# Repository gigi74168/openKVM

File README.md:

# openKVM

**Un mini KVM-over-IP ouvert, matériel compris, sans écran.** Tu le branches sur le HDMI et l'USB d'une machine, et tu la
pilotes depuis un navigateur : image, clavier, souris, démarrage sur une image ISO, jusque dans le BIOS.
Sur le boîtier : deux LED et un bouton, rien d'autre.

| Carte (pré-placement) | Boîtier (concept) |
|---|---|
|  |  |

> ⚠️ **État du projet : en conception.** Rien n'a encore été fabriqué ni testé. Les images ci-dessus sont des
> **rendus** : la carte est pré-placée mais **pas routée**, et le boîtier est un concept. Ne lance aucune fabrication
> à partir de ces fichiers sans la revue humaine décrite dans [`docs/04`](docs/04-schema-electronique.md#6-points-à-faire-relire-par-un-humain-avant-fabrication).

## En bref

| | openKVM v1 (visé) | JetKVM Mini (référence) |
|---|---|---|
| SoC | ESP32-P4NRW32X, 32 Mo de PSRAM | ESP32-P4X, 32 Mo de PSRAM |
| Vidéo | HDMI 1080p30 / 720p60, H.264 matériel | idem |
| Capture | TC358743, CSI-2 2 voies | idem |
| Réseau | Ethernet 10/100 (IP101GRI) | idem |
| USB cible | USB 2.0 High Speed : clavier, souris, stockage, audio | idem |
| microSD | Slot UHS-I (ISO plus rapides, à mesurer) | Slot standard |
| Écran | **Aucun** : LED d'alimentation + LED d'état, appareil trouvé par son nom réseau (mDNS, à venir avec le firmware) | IPS 240 × 240 |
| Boutons | 1 latéral (réinitialisation) + BOOT interne | 2 latéraux |
| Taille | PCB 45 × 45 mm ; boîtier ≈ 49,6 × 49,6 × 21,5 mm imprimé en 3D | 42 × 42 × 23 mm, aluminium |
| Matériel | **Ouvert : CERN-OHL-S-2.0** | Non publié |
| Firmware | Fork MIT du firmware du Mini, pilote d'écran retiré (à venir) | MIT |
| Prix | Objectif < 39 $ : **hors d'atteinte à 5–8 cartes**, jouable vers 20 cartes (voir [`docs/05`](docs/05-bom-chiffree.md)) | 39 $ ; 33 $ par 3 |

Pas de Gigabit en v1 : ni l'ESP32-P4 ni le RV1106 du JetKVM original ne le permettent.
L'explication est dans [`docs/00`](docs/00-decision-architecture.md).

## Architecture

## La carte

| Dessus | Vue arrière |
|---|---|
|  |  |

- **Arrière** : RJ45, HDMI, USB-C vers la machine cible.
- **Gauche** : USB-C « EXT » (alimentation, flashage, debug).
- **Droite** : microSD et bouton FN.
- **Avant** : LED d'alimentation (verte) et LED d'état (jaune).
- **Dessus** : capot plein, ouïes d'aération.

Le fichier [`hardware/openkvm.kicad_pcb`](hardware/openkvm.kicad_pcb) contient le contour, les 180 composants et tous
les nets. Les connecteurs et les puces principales sont placés ; **le routage reste à faire**.

## Le schéma

Six pages, disponibles en [PDF](hardware/exports/openkvm-schema.pdf) et dans KiCad 9.

| | |
|---|---|
|  Alimentation |  ESP32-P4 |
|  Capture HDMI |  Ethernet |
|  Périphériques |  Vue d'ensemble |

Le schéma est généré depuis une description texte ([`design.py`](hardware/scripts/design.py)), puis KiCad en
ré-extrait la netlist pour la comparer à la source : **706 broches, 0 différence**.

## Le boîtier

| Arrière | Avant et côté droit |
|---|---|
|  |  |

[`mechanical/openkvm-boitier-concept.scad`](mechanical/openkvm-boitier-concept.scad) est un modèle **paramétrique OpenSCAD**
qui sert d'aperçu : coque, capot plein à ouïes, découpes des connecteurs, deux trous de LED en façade. Les cotes définitives viendront au livrable 7,
une fois la carte routée. Pour ta propre CAO, la carte avec tous ses composants est dans
[`mechanical/openkvm-pcb-preplacement.step.zip`](mechanical/openkvm-pcb-preplacement.step.zip) (STEP, 3,3 Mo compressé)
et en [`GLB`](mechanical/openkvm-pcb-preplacement.glb) pour Blender ou un visualiseur web.

### Modèles 3D des composants

Chaque composant a un modèle dans [`hardware/lib/openkvm.3dshapes/`](hardware/lib/openkvm.3dshapes/) : 16 en **STEP et VRML**
(pièces LCSC, issues d'EasyEDA) et le BGA du TC358743, dessiné ici ([`gen_3d_bga.py`](hardware/scripts/gen_3d_bga.py)).
Deux sont **approximatifs**, à remplacer par ceux du fabricant pour tes cotes définitives :

- **TC358743 (BGA-64)** : corps 6 × 6 mm, épaisseur générique de 0,75 mm, **hauteur non vérifiée** sur la fiche technique ;
- **Oscillateur 27 MHz (Y2)** : forme générique 3,2 × 2,5 mm empruntée à l'oscillateur 40 MHz.

Le BGA n'existe qu'en VRML (KiCad ne sait pas l'exporter seul en STEP) ; il est inclus dans le STEP de la carte.

## Contenu du dépôt

```
docs/                       Les livrables, un par étape, avec leurs sources
  00-decision-architecture.md   Pourquoi ESP32-P4 et pas de Gigabit
  01-recherche-kvm-existants.md Comparatif JetKVM, NanoKVM, PicoKVM, PiKVM, Comet
  02-choix-soc-capture.md       ESP32-P4X et TC358743 : prix, stock, risques
  03-cahier-des-charges.md      Exigences, interfaces, budget de courant
  04-schema-electronique.md     Schéma, notes par bloc, points à relire
  05-bom-chiffree.md            BOM chiffrée, coût par carte, contraintes JLCPCB
  images/                       Rendus et diagrammes (sources dans images/src/)
hardware/                   Projet KiCad 9
  openkvm.kicad_pro/.kicad_sch  Schéma (5 feuilles)
  openkvm.kicad_pcb             Carte pré-placée, non routée
  fabrication/                  BOM JLCPCB, BOM chiffrée, instantané des prix
  exports/                      PDF du schéma, netlist et liste de composants en CSV
  lib/                          Symboles, empreintes, modèles 3D (.wrl + .step)
  scripts/                      design.py (source), générateurs, vérification
  build.sh                      Régénère tout
mechanical/                 Concept de boîtier (OpenSCAD), carte en STEP et en GLB
LICENSES/, LICENSE.md, NOTICE.md
```

## Utiliser les fichiers

**Ouvrir le projet** : KiCad 9, puis `hardware/openkvm.kicad_pro`.

**Régénérer** après une modification de `design.py` (il faut KiCad 9 avec `kicad-cli` et le module Python `pcbnew`) :

```bash
cd hardware && ./build.sh
```

Attention : `build.sh` réécrit `openkvm.kicad_pcb`. Une fois ton routage commencé, ne relance que le schéma
(`python3 scripts/gen_kicad.py`) et utilise « Mettre à jour le PCB depuis le schéma » dans KiCad.

**Commander chez JLCPCB**, quand la carte sera routée et relue :

| Fichier demandé par JLCPCB | Où | État |
|---|---|---|
| BOM | [`hardware/fabrication/openkvm-bom-jlcpcb.csv`](hardware/fabrication/openkvm-bom-jlcpcb.csv) | Prête, 1 ligne sans code LCSC (TC358743, à fournir) |
| Gerbers et perçages | À exporter depuis KiCad après routage | À faire |
| Fichier de placement (CPL) | À exporter depuis KiCad après routage | À faire |

## Avancement

| # | Livrable | État |
|---|---|---|
| 0 | Décision d'architecture | ✅ [`docs/00`](docs/00-decision-architecture.md) |
| 1 | Recherche sur les KVM existants | ✅ [`docs/01`](docs/01-recherche-kvm-existants.md) |
| 2 | Choix du SoC et de la puce de capture | ✅ [`docs/02`](docs/02-choix-soc-capture.md) |
| 3 | Cahier des charges et diagramme de blocs | ✅ [`docs/03`](docs/03-cahier-des-charges.md) |
| 4 | Schéma électronique | 🟡 rév. 0.2 (sans écran), à relire : [`docs/04`](docs/04-schema-electronique.md) |
| 5 | BOM chiffrée (prix sur 5 pièces) | 🟡 rév. 0.2 (sans écran), à valider : [`docs/05`](docs/05-bom-chiffree.md) |
| 6 | Spécifications de layout | ⏳ |
| 7 | Cotes du boîtier | ⏳ concept disponible |
| 8 | Firmware (fork du JetKVM Mini) | ⏳ |
| 9 | Plan de test et de mise en route | ⏳ |

## Risques connus

- **TC358743 obsolète** : introuvable chez LCSC, à acheter chez un broker (risque de contrefaçon).
- **HDMI, USB High Speed, MIPI** : signaux rapides, le routage demandera des impédances contrôlées.
- **BGA au pas de 0,65 mm** et QFN-104 : assemblage délicat, radiographie conseillée.
- **Consommation** : 0,52 à 0,57 A estimés sous 5 V, au-dessus des 500 mA d'un port USB 2.0.
- **Pas d'écran** : sans mDNS ou accès au routeur, l'adresse IP de l'appareil ne se devine pas. À traiter dans le firmware.
- **Aucune certification CE/FCC** : prototypes à usage personnel.
- **HDCP non géré** : les contenus protégés donneront un écran noir.

## Licences

Matériel sous **CERN-OHL-S-2.0**, scripts sous **MIT**, documentation sous **CC-BY-SA-4.0**.
Détail dans [`LICENSE.md`](LICENSE.md), éléments repris de tiers dans [`NOTICE.md`](NOTICE.md).

« JetKVM » est une marque de BuildJet, Inc. openKVM est un projet indépendant.

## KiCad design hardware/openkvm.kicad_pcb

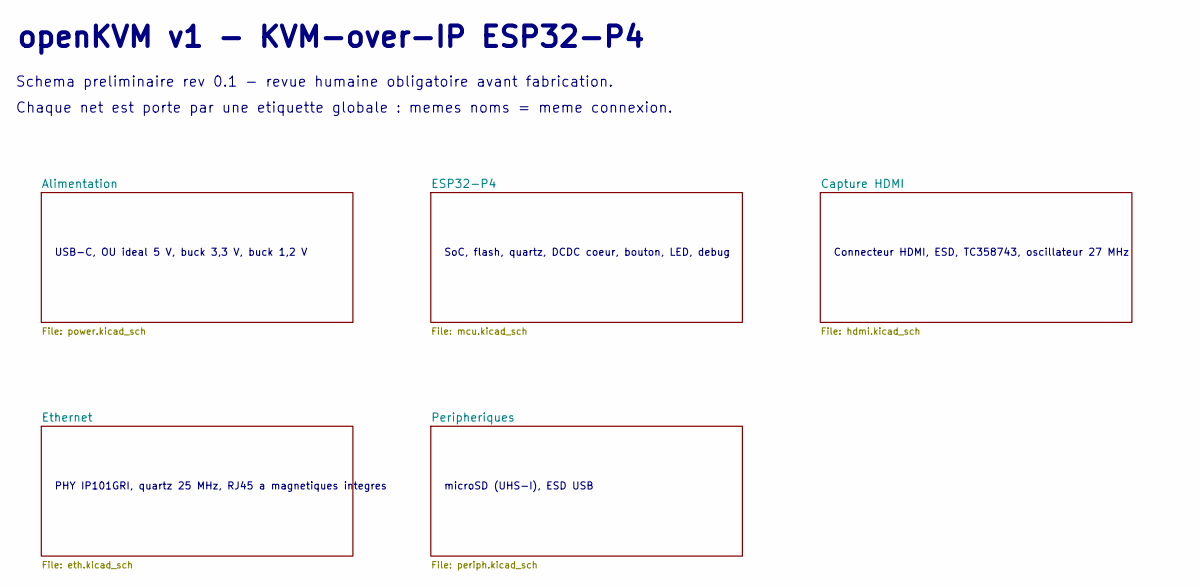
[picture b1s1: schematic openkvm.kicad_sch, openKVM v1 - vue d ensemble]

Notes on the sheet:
openKVM v1 - KVM-over-IP ESP32-P4
Schema preliminaire rev 0.1 - revue humaine obligatoire avant fabrication.
Chaque net est porte par une etiquette globale : memes noms = meme connexion.
USB-C, OU ideal 5 V, buck 3,3 V, buck 1,2 V
SoC, flash, quartz, DCDC coeur, bouton, LED, debug
Connecteur HDMI, ESD, TC358743, oscillateur 27 MHz
PHY IP101GRI, quartz 25 MHz, RJ45 a magnetiques integres
microSD (UHS-I), ESD USB

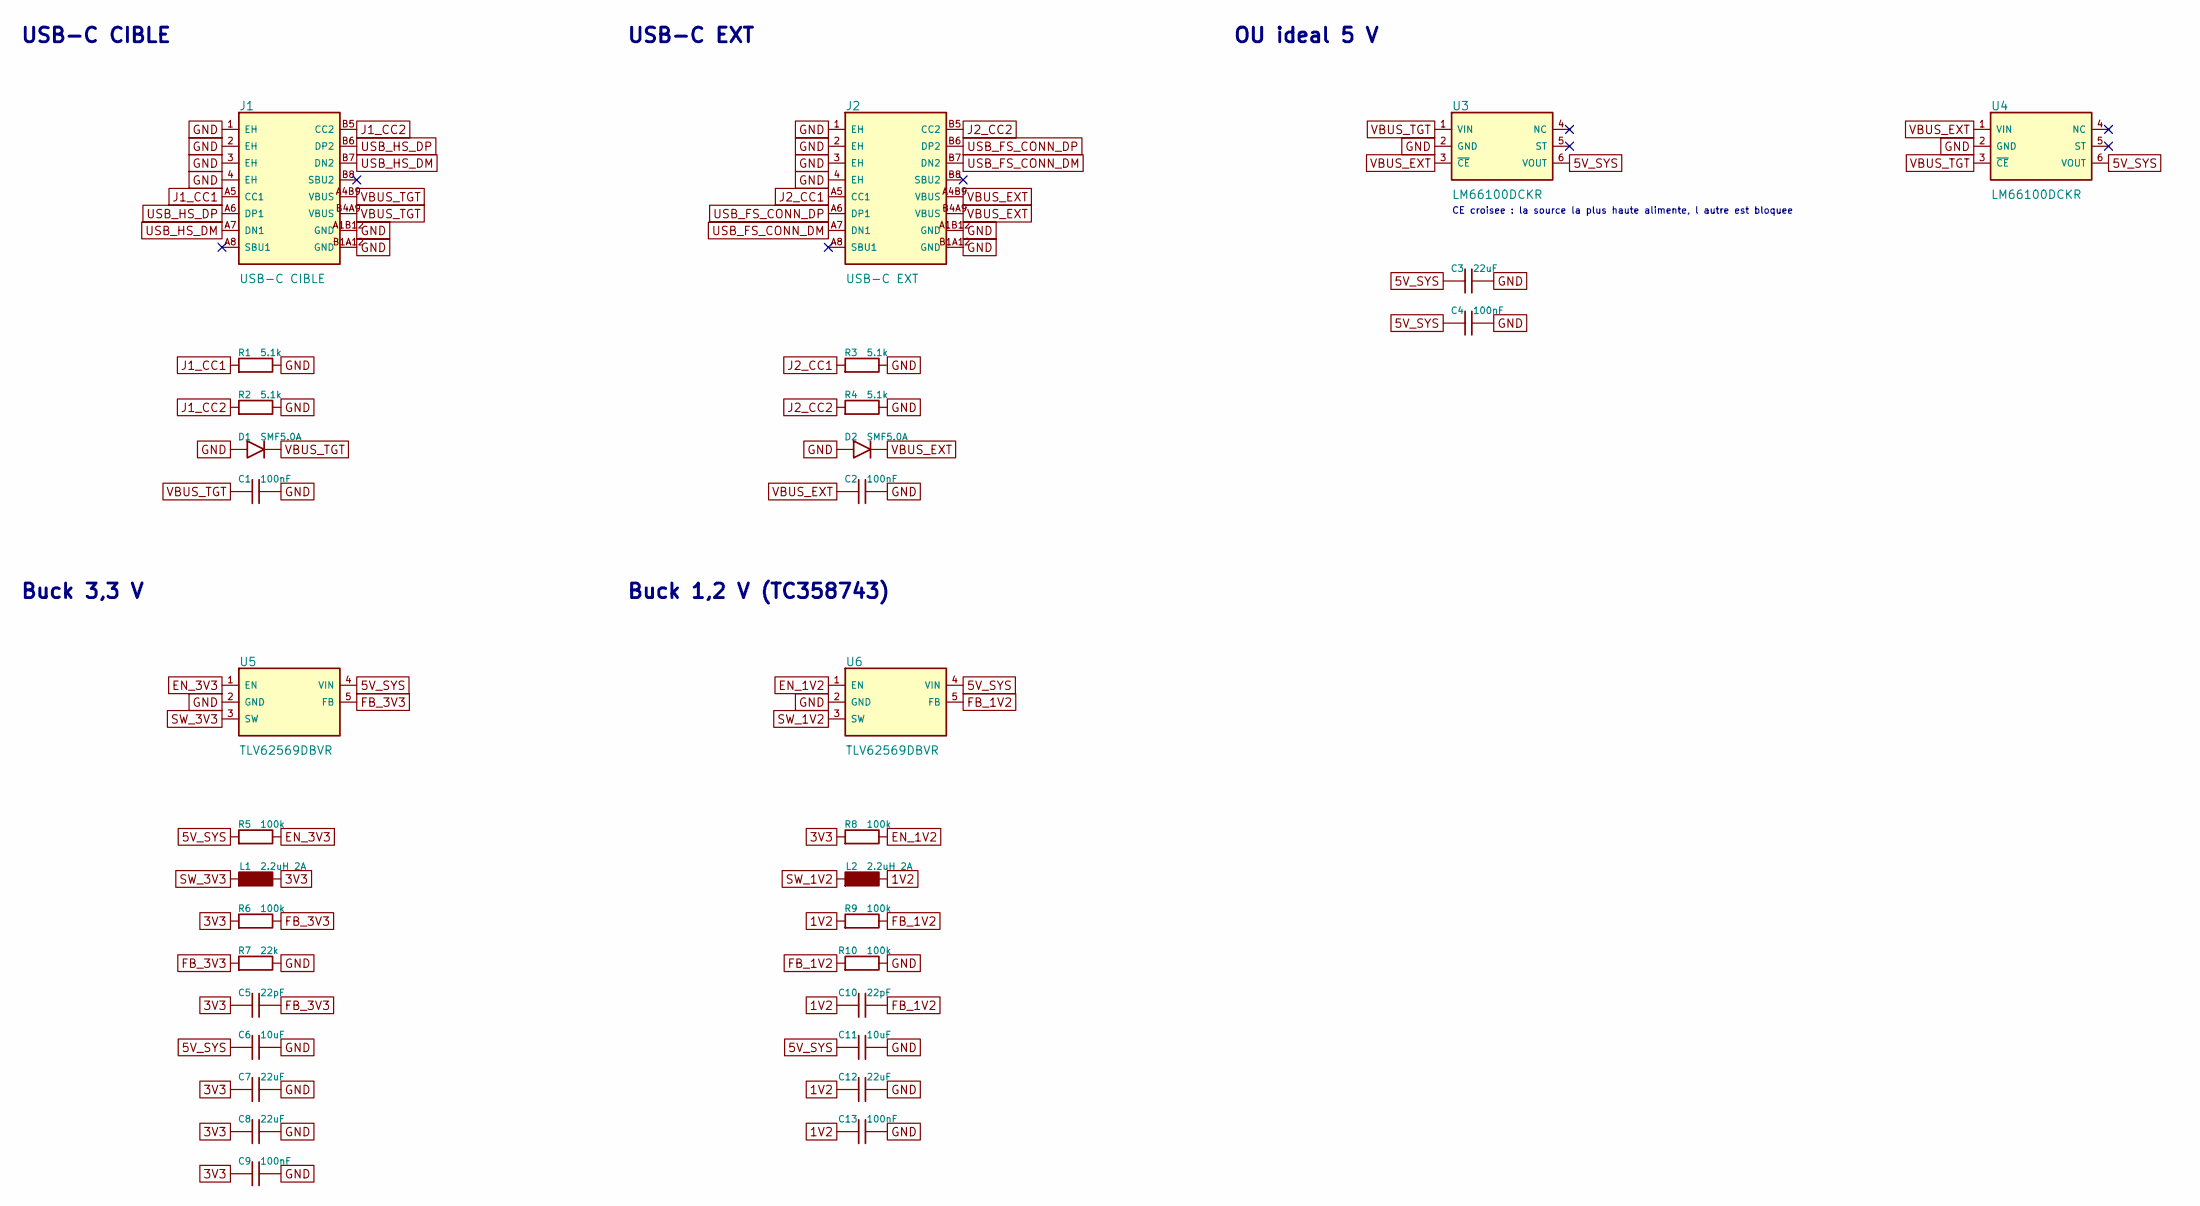
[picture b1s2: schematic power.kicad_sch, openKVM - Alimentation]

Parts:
C1, C2, C4, C9, C13: 100nF; C_0402_1005Metric; MPN CL05B104KO5NNNC; LCSC C1525
C3, C7, C8, C12: 22uF; C_0805_2012Metric; MPN CL21A226MAQNNNE; LCSC C45783
C5, C10: 22pF; C_0402_1005Metric; MPN 0402CG220J500NT; LCSC C1555
C6, C11: 10uF; C_0603_1608Metric; MPN CL10A106KP8NNNC; LCSC C19702
D1, D2: SMF5.0A; SOD-123FL_L2.7-W1.8-LS3.8-RD; MPN SMF5.0A; LCSC C19077497
J1: USB-C CIBLE; USB-C_SMD-TYPE-C-31-M-12_1; MPN TYPE-C-31-M-12; LCSC C165948
J2: USB-C EXT; USB-C_SMD-TYPE-C-31-M-12_1; MPN TYPE-C-31-M-12; LCSC C165948
L1, L2: 2.2uH 2A; IND-SMD_L3.0-W3.0; MPN SWPA3015S2R2MT; LCSC C43389
R1, R2, R3, R4: 5.1k; R_0402_1005Metric; MPN 0402WGF5101TCE; LCSC C25905
R5, R6, R8, R9, R10: 100k; R_0402_1005Metric; MPN 0402WGF1003TCE; LCSC C25741
R7: 22k; R_0402_1005Metric; MPN 0402WGF2202TCE; LCSC C25768
U3, U4: LM66100DCKR; SC-70-6_L2.0-W1.3-P0.65-LS2.1-BL; MPN LM66100DCKR; LCSC C2869734
U5, U6: TLV62569DBVR; SOT-23-5_L3.0-W1.7-P0.95-LS2.8-BR; MPN TLV62569DBVR; LCSC C141836

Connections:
1V2: C10.1, C12.1, C13.1, L2.2, R9.1; also elsewhere on the board
3V3: C5.1, C7.1, C8.1, C9.1, L1.2, R6.1, R8.1; also elsewhere on the board
5V_SYS: C3.1, C4.1, C6.1, C11.1, R5.1, U3.6 (VOUT), U4.6 (VOUT), U5.4 (VIN), U6.4 (VIN); also elsewhere on the board
EN_1V2: R8.2, U6.1 (EN)
EN_3V3: R5.2, U5.1 (EN)
FB_1V2: C10.2, R9.2, R10.1, U6.5 (FB)
FB_3V3: C5.2, R6.2, R7.1, U5.5 (FB)
GND: C1.2, C2.2, C3.2, C4.2, C6.2, C7.2, C8.2, C9.2, C11.2, C12.2, C13.2, D1.2, D2.2, J1.1 (EH), J1.2 (EH), J1.3 (EH), J1.4 (EH), J1.A1B12 (GND), J1.B1A12 (GND), J2.1 (EH), J2.2 (EH), J2.3 (EH), J2.4 (EH), J2.A1B12 (GND), J2.B1A12 (GND), R1.2, R2.2, R3.2, R4.2, R7.2, R10.2, U3.2 (GND), U4.2 (GND), U5.2 (GND), U6.2 (GND); also elsewhere on the board
J1_CC1: J1.A5 (CC1), R1.1; also elsewhere on the board
J1_CC2: J1.B5 (CC2), R2.1; also elsewhere on the board
J2_CC1: J2.A5 (CC1), R3.1; also elsewhere on the board
J2_CC2: J2.B5 (CC2), R4.1; also elsewhere on the board
SW_1V2: L2.1, U6.3 (SW)
SW_3V3: L1.1, U5.3 (SW)
USB_FS_CONN_DM: J2.A7 (DN1), J2.B7 (DN2); also elsewhere on the board
USB_FS_CONN_DP: J2.A6 (DP1), J2.B6 (DP2); also elsewhere on the board
USB_HS_DM: J1.A7 (DN1), J1.B7 (DN2); also elsewhere on the board
USB_HS_DP: J1.A6 (DP1), J1.B6 (DP2); also elsewhere on the board
VBUS_EXT: C2.1, D2.1, J2.A4B9 (VBUS), J2.B4A9 (VBUS), U3.3 (~CE), U4.1 (VIN)
VBUS_TGT: C1.1, D1.1, J1.A4B9 (VBUS), J1.B4A9 (VBUS), U3.1 (VIN), U4.3 (~CE)

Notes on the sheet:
USB-C CIBLE
USB-C EXT
OU ideal 5 V
CE croisee : la source la plus haute alimente, l autre est bloquee
Buck 3,3 V
Buck 1,2 V (TC358743)

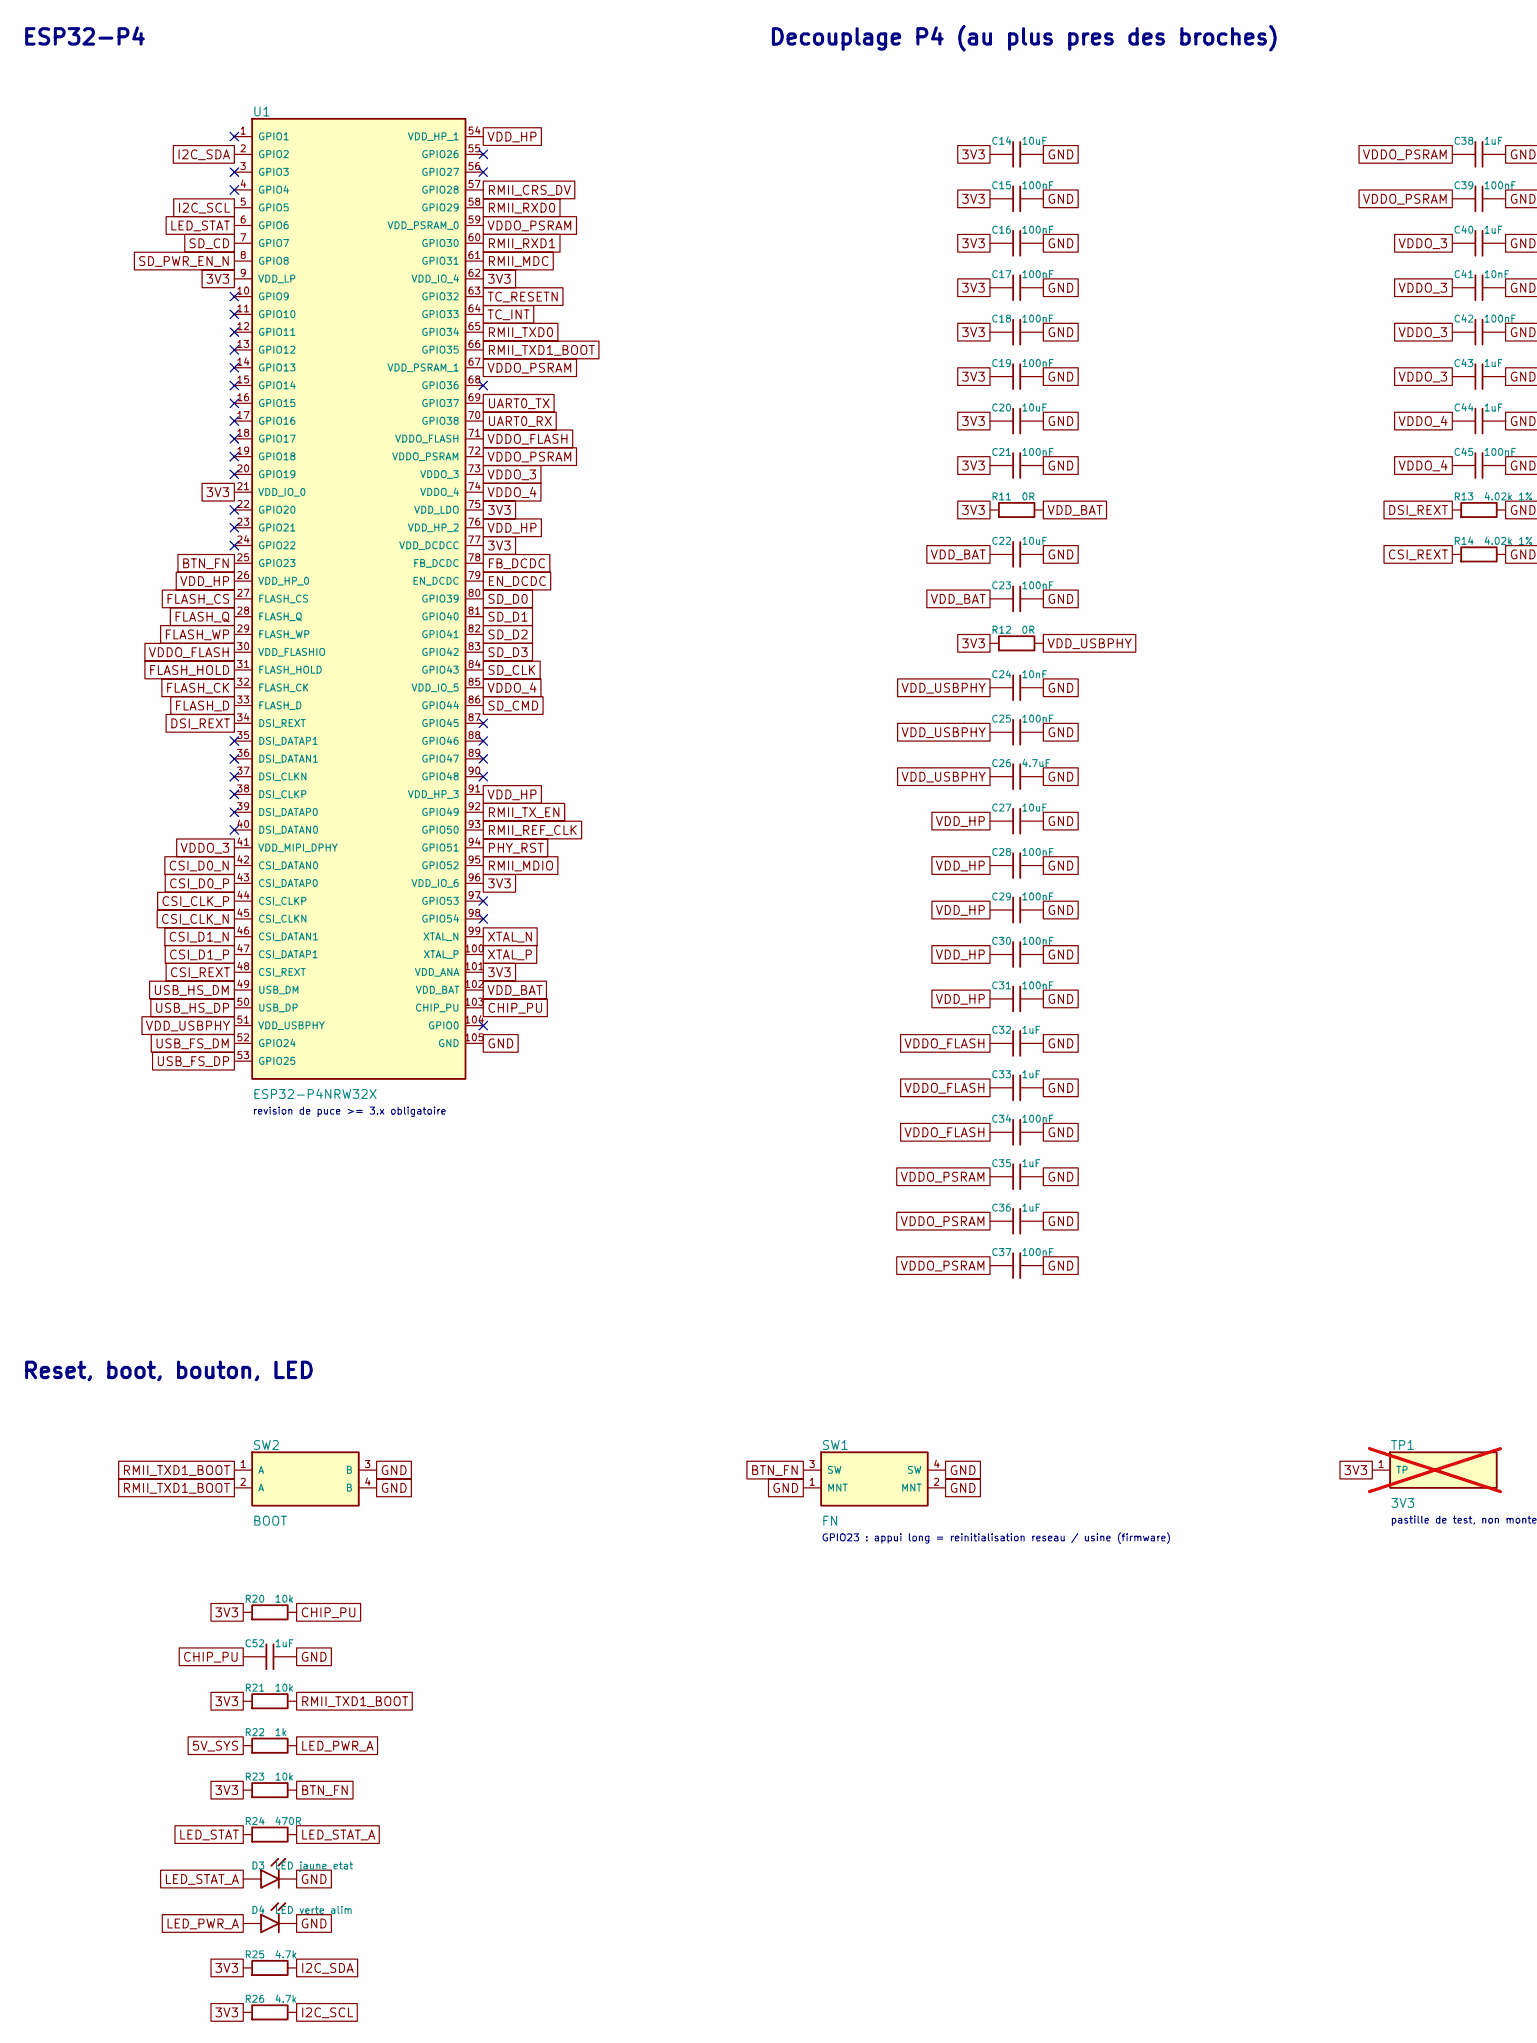
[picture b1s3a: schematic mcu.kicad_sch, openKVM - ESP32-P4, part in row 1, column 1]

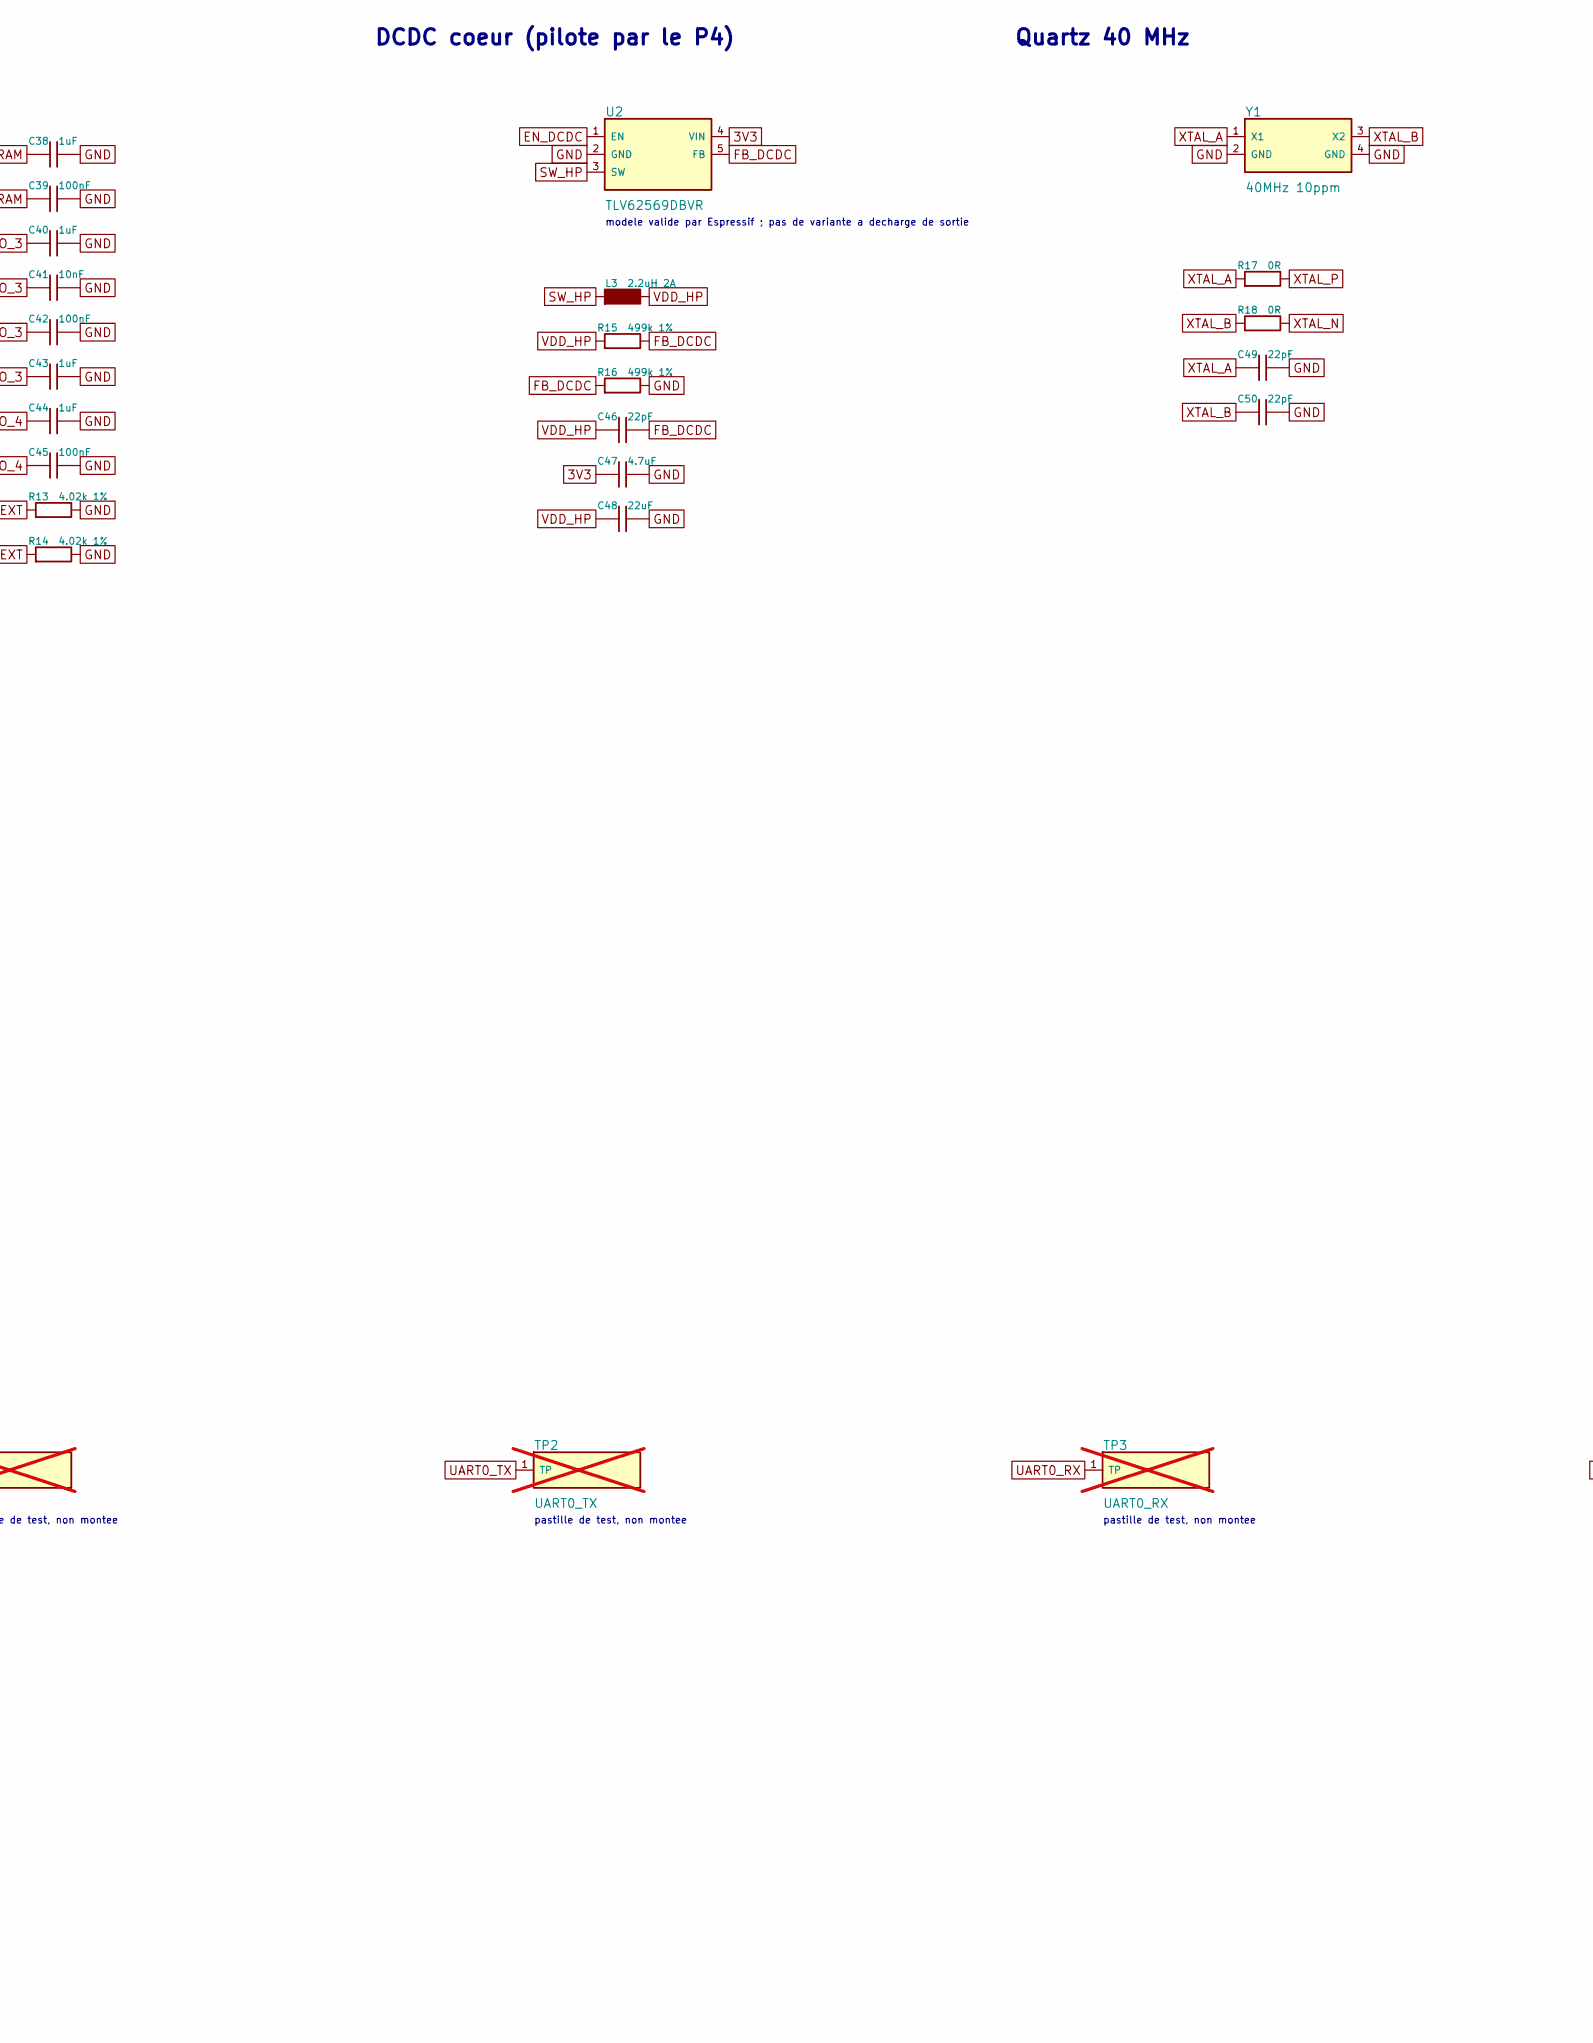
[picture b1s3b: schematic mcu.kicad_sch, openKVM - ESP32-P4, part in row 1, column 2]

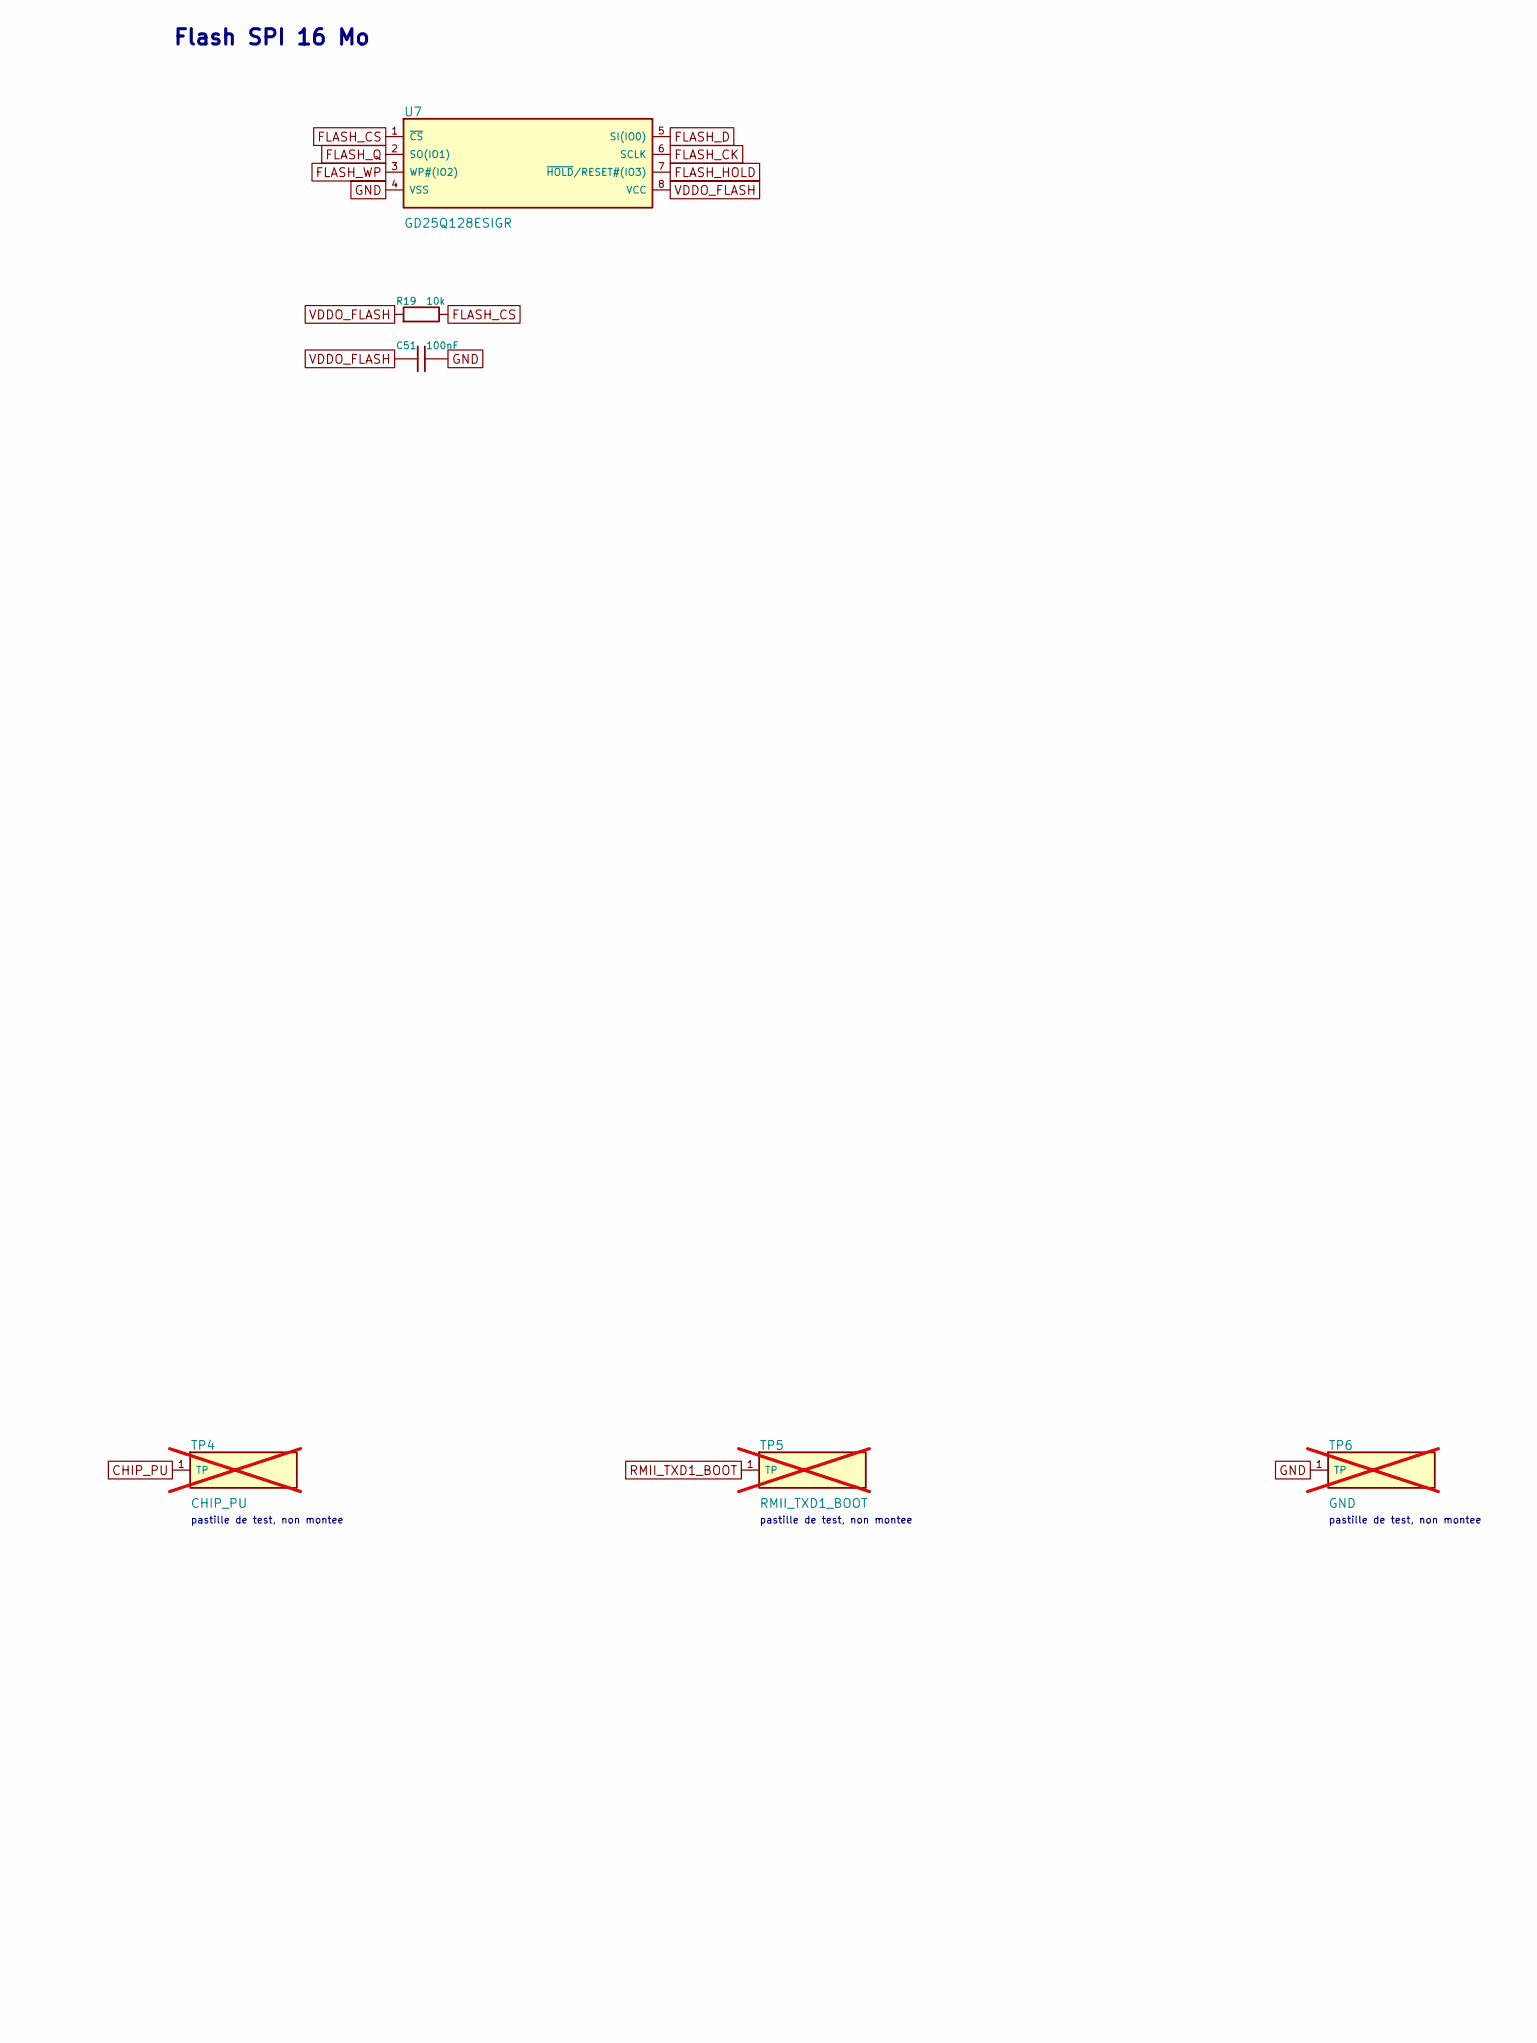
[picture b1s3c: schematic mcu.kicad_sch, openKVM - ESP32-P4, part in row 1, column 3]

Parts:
C14, C20, C22, C27: 10uF; C_0603_1608Metric; MPN CL10A106KP8NNNC; LCSC C19702
C15, C16, C17, C18, C19, C21, C23, C25, C28, C29, C30, C31, C34, C37, C39, C42, C45, C51: 100nF; C_0402_1005Metric; MPN CL05B104KO5NNNC; LCSC C1525
C24, C41: 10nF; C_0402_1005Metric; MPN CL05B103KB5NNNC; LCSC C15195
C26, C47: 4.7uF; C_0603_1608Metric; MPN CL10A475KO8NNNC; LCSC C19666
C32, C33, C35, C36, C38, C40, C43, C44, C52: 1uF; C_0402_1005Metric; MPN CL05A105KA5NQNC; LCSC C52923
C46, C49, C50: 22pF; C_0402_1005Metric; MPN 0402CG220J500NT; LCSC C1555
C48: 22uF; C_0805_2012Metric; MPN CL21A226MAQNNNE; LCSC C45783
D3: LED jaune etat; LED0603-R-RD; MPN KT-0603Y; LCSC C2287
D4: LED verte alim; LED0603-RD; MPN KT-0603G; LCSC C12624
L3: 2.2uH 2A; IND-SMD_L3.0-W3.0; MPN SWPA3015S2R2MT; LCSC C43389
R11, R12, R17, R18: 0R; R_0402_1005Metric; MPN 0402WGF0000TCE; LCSC C17168
R13, R14: 4.02k 1%; R_0402_1005Metric; MPN 0402WGF4021TCE; LCSC C43251
R15, R16: 499k 1%; R_0402_1005Metric; MPN 0402WGF4993TCE; LCSC C25793
R19, R20, R21, R23: 10k; R_0402_1005Metric; MPN 0402WGF1002TCE; LCSC C25744
R22: 1k; R_0402_1005Metric; MPN 0402WGF1001TCE; LCSC C11702
R24: 470R; R_0402_1005Metric; MPN 0402WGF4700TCE; LCSC C25117
R25, R26: 4.7k; R_0402_1005Metric; MPN 0402WGF4701TCE; LCSC C25900
SW1: FN; KEY-SMD_TS-1101VS-C-A-A; MPN TS-1101VS-C-A-A; LCSC C318936
SW2: BOOT; SW-SMD_4P-L5.1-W5.1-P3.70-LS6.5-TL_H1.5; MPN TS-1187A-B-A-B; LCSC C318884
TP1: 3V3; TestPoint_Pad_D1.0mm; not fitted
TP2: UART0_TX; TestPoint_Pad_D1.0mm; not fitted
TP3: UART0_RX; TestPoint_Pad_D1.0mm; not fitted
TP4: CHIP_PU; TestPoint_Pad_D1.0mm; not fitted
TP5: RMII_TXD1_BOOT; TestPoint_Pad_D1.0mm; not fitted
TP6: GND; TestPoint_Pad_D1.0mm; not fitted
U1: ESP32-P4NRW32X; QFN-104_L10.0-W10.0-P0.35-TL-EP7.5; MPN ESP32-P4NRW32X; LCSC C54540373
U2: TLV62569DBVR; SOT-23-5_L3.0-W1.7-P0.95-LS2.8-BR; MPN TLV62569DBVR; LCSC C141836
U7: GD25Q128ESIGR; SOP-8_L5.3-W5.3-P1.27-LS8.0-BL; MPN GD25Q128ESIGR; LCSC C2928891
Y1: 40MHz 10ppm; OSC-SMD_4P-L3.2-W2.5-BL_SIT8008BI; MPN X322540MPB4SI; LCSC C9010

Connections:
3V3: C14.1, C15.1, C16.1, C17.1, C18.1, C19.1, C20.1, C21.1, C47.1, R11.1, R12.1, R20.1, R21.1, R23.1, R25.1, R26.1, TP1.1, U1.9 (VDD_LP), U1.21 (VDD_IO_0), U1.62 (VDD_IO_4), U1.75 (VDD_LDO), U1.77 (VDD_DCDCC), U1.96 (VDD_IO_6), U1.101 (VDD_ANA), U2.4 (VIN); also elsewhere on the board
5V_SYS: R22.1; also elsewhere on the board
BTN_FN: R23.2, SW1.3 (SW), U1.25 (GPIO23)
CHIP_PU: C52.1, R20.2, TP4.1, U1.103 (CHIP_PU)
CSI_CLK_N: U1.45 (CSI_CLKN); also elsewhere on the board
CSI_CLK_P: U1.44 (CSI_CLKP); also elsewhere on the board
CSI_D0_N: U1.42 (CSI_DATAN0); also elsewhere on the board
CSI_D0_P: U1.43 (CSI_DATAP0); also elsewhere on the board
CSI_D1_N: U1.46 (CSI_DATAN1); also elsewhere on the board
CSI_D1_P: U1.47 (CSI_DATAP1); also elsewhere on the board
CSI_REXT: R14.1, U1.48 (CSI_REXT)
DSI_REXT: R13.1, U1.34 (DSI_REXT)
EN_DCDC: U1.79 (EN_DCDC), U2.1 (EN)
FB_DCDC: C46.2, R15.2, R16.1, U1.78 (FB_DCDC), U2.5 (FB)
FLASH_CK: U1.32 (FLASH_CK), U7.6 (SCLK)
FLASH_CS: R19.2, U1.27 (FLASH_CS), U7.1 (~CS)
FLASH_D: U1.33 (FLASH_D), U7.5 (SI(IO0))
FLASH_HOLD: U1.31 (FLASH_HOLD), U7.7 (~HOLD/RESET#(IO3))
FLASH_Q: U1.28 (FLASH_Q), U7.2 (SO(IO1))
FLASH_WP: U1.29 (FLASH_WP), U7.3 (WP#(IO2))
GND: C14.2, C15.2, C16.2, C17.2, C18.2, C19.2, C20.2, C21.2, C22.2, C23.2, C24.2, C25.2, C26.2, C27.2, C28.2, C29.2, C30.2, C31.2, C32.2, C33.2, C34.2, C35.2, C36.2, C37.2, C38.2, C39.2, C40.2, C41.2, C42.2, C43.2, C44.2, C45.2, C47.2, C48.2, C49.2, C50.2, C51.2, C52.2, D3.2, D4.1, R13.2, R14.2, R16.2, SW1.1 (MNT), SW1.2 (MNT), SW1.4 (SW), SW2.3 (B), SW2.4 (B), TP6.1, U1.105 (GND), U2.2 (GND), U7.4 (VSS), Y1.2 (GND), Y1.4 (GND); also elsewhere on the board
I2C_SCL: R26.2, U1.5 (GPIO5); also elsewhere on the board
I2C_SDA: R25.2, U1.2 (GPIO2); also elsewhere on the board
LED_PWR_A: D4.2, R22.2
LED_STAT: R24.1, U1.6 (GPIO6)
LED_STAT_A: D3.1, R24.2
PHY_RST: U1.94 (GPIO51); also elsewhere on the board
RMII_CRS_DV: U1.57 (GPIO28); also elsewhere on the board
RMII_MDC: U1.61 (GPIO31); also elsewhere on the board
RMII_MDIO: U1.95 (GPIO52); also elsewhere on the board
RMII_REF_CLK: U1.93 (GPIO50); also elsewhere on the board
RMII_RXD0: U1.58 (GPIO29); also elsewhere on the board
RMII_RXD1: U1.60 (GPIO30); also elsewhere on the board
RMII_TXD0: U1.65 (GPIO34); also elsewhere on the board
RMII_TXD1_BOOT: R21.2, SW2.1 (A), SW2.2 (A), TP5.1, U1.66 (GPIO35); also elsewhere on the board
RMII_TX_EN: U1.92 (GPIO49); also elsewhere on the board
SD_CD: U1.7 (GPIO7); also elsewhere on the board
SD_CLK: U1.84 (GPIO43); also elsewhere on the board
SD_CMD: U1.86 (GPIO44); also elsewhere on the board
SD_D0: U1.80 (GPIO39); also elsewhere on the board
SD_D1: U1.81 (GPIO40); also elsewhere on the board
SD_D2: U1.82 (GPIO41); also elsewhere on the board
SD_D3: U1.83 (GPIO42); also elsewhere on the board
SD_PWR_EN_N: U1.8 (GPIO8); also elsewhere on the board
SW_HP: L3.1, U2.3 (SW)
TC_INT: U1.64 (GPIO33); also elsewhere on the board
TC_RESETN: U1.63 (GPIO32); also elsewhere on the board
UART0_RX: TP3.1, U1.70 (GPIO38)
UART0_TX: TP2.1, U1.69 (GPIO37)
USB_FS_DM: U1.52 (GPIO24); also elsewhere on the board
USB_FS_DP: U1.53 (GPIO25); also elsewhere on the board
USB_HS_DM: U1.49 (USB_DM); also elsewhere on the board
USB_HS_DP: U1.50 (USB_DP); also elsewhere on the board
VDDO_3: C40.1, C41.1, C42.1, C43.1, U1.41 (VDD_MIPI_DPHY), U1.73 (VDDO_3); also elsewhere on the board
VDDO_4: C44.1, C45.1, U1.74 (VDDO_4), U1.85 (VDD_IO_5); also elsewhere on the board
VDDO_FLASH: C32.1, C33.1, C34.1, C51.1, R19.1, U1.30 (VDD_FLASHIO), U1.71 (VDDO_FLASH), U7.8 (VCC)
VDDO_PSRAM: C35.1, C36.1, C37.1, C38.1, C39.1, U1.59 (VDD_PSRAM_0), U1.67 (VDD_PSRAM_1), U1.72 (VDDO_PSRAM)
VDD_BAT: C22.1, C23.1, R11.2, U1.102 (VDD_BAT)
VDD_HP: C27.1, C28.1, C29.1, C30.1, C31.1, C46.1, C48.1, L3.2, R15.1, U1.26 (VDD_HP_0), U1.54 (VDD_HP_1), U1.76 (VDD_HP_2), U1.91 (VDD_HP_3)
VDD_USBPHY: C24.1, C25.1, C26.1, R12.2, U1.51 (VDD_USBPHY)
XTAL_A: C49.1, R17.1, Y1.1 (X1)
XTAL_B: C50.1, R18.1, Y1.3 (X2)
XTAL_N: R18.2, U1.99 (XTAL_N)
XTAL_P: R17.2, U1.100 (XTAL_P)

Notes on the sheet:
ESP32-P4
revision de puce >= 3.x obligatoire
Decouplage P4 (au plus pres des broches)
DCDC coeur (pilote par le P4)
modele valide par Espressif ; pas de variante a decharge de sortie
Quartz 40 MHz
Flash SPI 16 Mo
Reset, boot, bouton, LED
GPIO23 : appui long = reinitialisation reseau / usine (firmware)
pastille de test, non montee

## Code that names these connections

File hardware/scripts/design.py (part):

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    G = 'Reset, boot, bouton, LED'
    d.R('3V3', 'CHIP_PU', '10k', S, G, note='RC de demarrage 10k / 1 uF ; pas de bouton RESET, CHIP_PU est sur la pastille TP4')
    d.C('CHIP_PU', '1uF', S, G)
    d.R('3V3', 'RMII_TXD1_BOOT', '10k', S, G, note='GPIO35 = strap BOOT, aussi RMII TXD1')
    d.part('SW2', 'SW4', 'BOOT', 'openkvm:SW-SMD_4P-L5.1-W5.1-P3.70-LS6.5-TL_H1.5', S, G,
           {1: 'RMII_TXD1_BOOT', 2: 'RMII_TXD1_BOOT', 3: 'GND', 4: 'GND'}, 'C318884', 'TS-1187A-B-A-B')
    # Pas d'ecran : un bouton lateral unique et deux LED remplacent l'affichage.
    d.R('5V_SYS', 'LED_PWR_A', '1k', S, G, note='LED verte (Vf ~3,1 V) sur le 5 V : ~1,9 mA. Sur 3,3 V elle serait presque eteinte')
    d.part('SW1', 'SWSIDE', 'FN', 'openkvm:KEY-SMD_TS-1101VS-C-A-A', S, G,
           {1: 'GND', 2: 'GND', 3: 'BTN_FN', 4: 'GND'}, 'C318936', 'TS-1101VS-C-A-A',
           note='GPIO23 : appui long = reinitialisation reseau / usine (firmware)')
    d.R('3V3', 'BTN_FN', '10k', S, G)
    d.R('LED_STAT', 'LED_STAT_A', '470R', S, G, note='LED jaune (Vf 2,4 V) depuis GPIO6 : ~1,9 mA')
    # Empreintes de la bibliotheque JLCPCB : la jaune est numerotee a l'envers de la verte (1 = anode).
    d.part('D3', 'LEDR', 'LED jaune etat', 'openkvm:LED0603-R-RD', S, G, {1: 'LED_STAT_A', 2: 'GND'},
           'C2287', 'KT-0603Y', note='1 = ANODE, 2 = cathode (numerotation JLCPCB) ; pilotee par le firmware')
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    d.R('3V3', 'ETH_RMII_SEL', '4.7k', S, G, note='strap : 1 = RMII')
    d.R('3V3', 'ETH_LED0', '4.7k', S, G, note='strap PHY_AD0 = 1 (adresse 1)')
    d.R('ETH_ISET', 'GND', '6.19k 1%', S, G)
    d.R('ETH_CLKO', 'RMII_REF_CLK', '33R', S, G, note='50 MHz vers GPIO50, au plus pres du PHY')
    d.R('3V3', 'RMII_MDIO', '4.7k', S, G)
    d.R('3V3', 'PHY_RST', '10k', S, G)
    d.decap('3V3', ['100nF'], S, G)                      # VDDIO (13)
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        d.R(f'SD_{sig}', f'SD_C_{sig}', '22R', S, G)
    for sig in ('CMD', 'D0', 'D1', 'D2', 'D3'):
        d.R('VDDO_4', f'SD_{sig}', '10k', S, G)
    d.R('3V3', 'SD_CD', '10k', S, G, note='detection de carte, GPIO7 (domaine 3,3 V)')
    d.part('Q1', 'PMOS', 'AO3401A', 'openkvm:SOT-23_L2.9-W1.3-P1.90-LS2.4-BR', S, G,
           {1: 'SD_PWR_EN_N', 2: '3V3', 3: 'SD_VDD'}, 'C15127', 'AO3401A',
           note='1 = G, 2 = S, 3 = D ; coupe la carte pour quitter le mode 1,8 V')
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

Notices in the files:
hardware/eth.kicad_sch:
openKVM - CERN-OHL-S-2.0
parts and their libraries:
License: Apache-2.0
